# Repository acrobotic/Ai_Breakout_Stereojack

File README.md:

## Ai\_Breakout\_TXB0108

PCB design files (EAGLE) for a breakout board of a 3.5mm audio jack (stereo).

## Description

For more details, check out the product page at:

   * https://acrobotic.com/brk-00005

Designed by ACROBOTIC Industries.  Please consider buying products from us to 
help fund future Open-Source projects like this! We’ll always put our best 
effort in every project, and release all our design files and code for you to 
use. 

## License

Released under the Creative Commons Attribution, Share-Alike license. Please 
check LICENSE.txt for more information. All text above must be included in any 
redistribution.

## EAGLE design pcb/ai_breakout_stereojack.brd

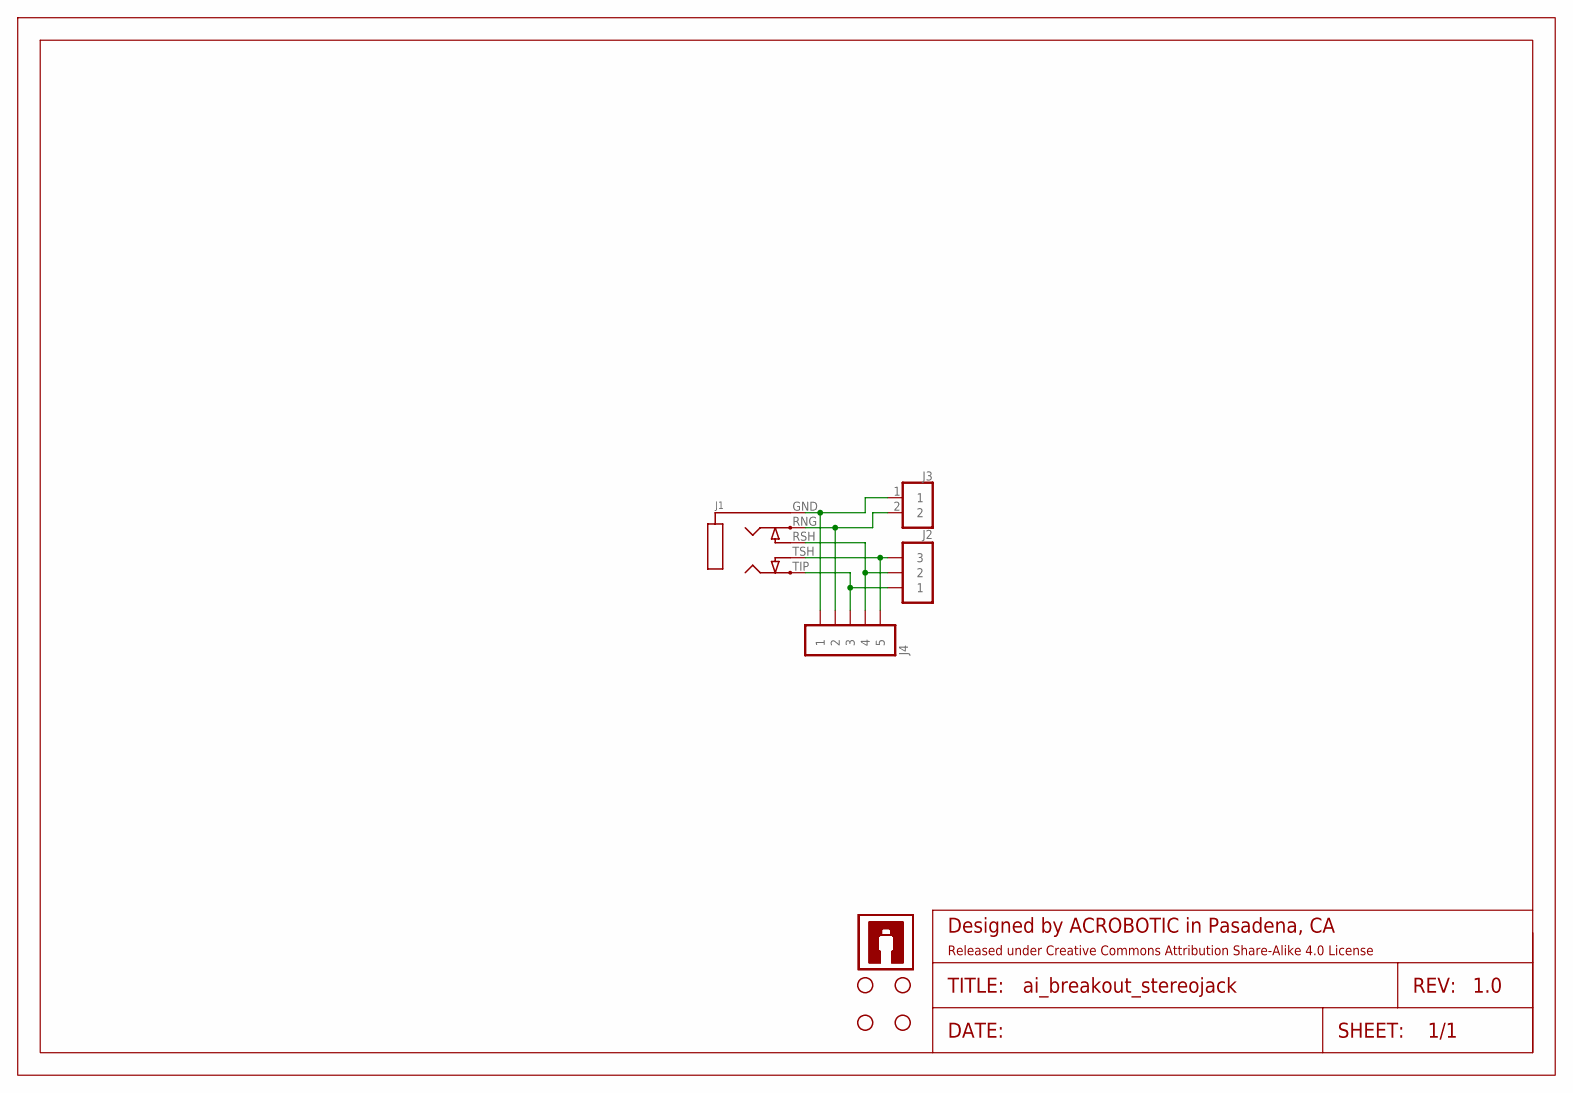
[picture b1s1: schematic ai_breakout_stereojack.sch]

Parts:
FRAME1: FRAME-LETTER; CREATIVE-COMMONS
J1: STEREOJACKSJ1-351XNG; SJ1-351XNG
J2: 1X03ST; 1X03-ST
J3: 1X02ST; 1X02-ST
J4: 1X05
STANDOFF1, STANDOFF2, STANDOFF3, STANDOFF4: STAND-OFF4; STAND-OFF-4
U$1, U$2: AI-LOGOXS; AI-LOGO-XS

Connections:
GND: J1.GND, J3.1, J4.1
RNG: J1.RNG, J3.2, J4.2
RSH: J1.RSH, J2.2, J4.4
TIP: J1.TIP, J2.1, J4.3
TSH: J1.TSH, J2.3, J4.5

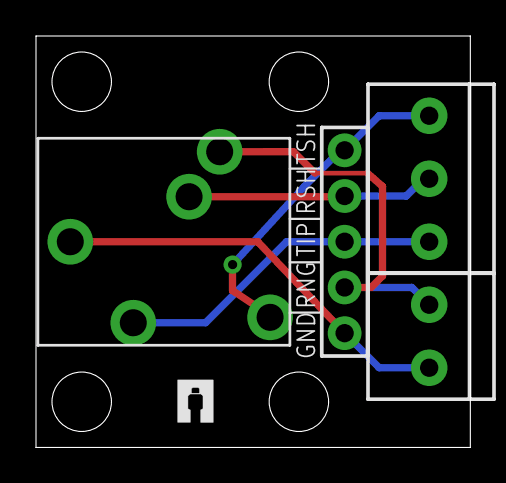
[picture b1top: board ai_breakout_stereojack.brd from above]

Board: 2 copper layers, 24.1 x 22.9 mm, 11 parts (1 on the bottom side), 5 nets.

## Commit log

2015-09-29 First commit.

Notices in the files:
parts and their libraries:
Ai_Miscellany: Attribution Share-Alike 4.0 License
Ai_Miscellany: https://creativecommons.org/licenses/by-sa/4.0
Ai_Miscellany: Released under Creative Commons Attribution Share-Alike 4.0 License
